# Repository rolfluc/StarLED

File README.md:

Simply a 4x Series 2x Parallel LED board to use the star shaped board designs that are seen by OSRAM

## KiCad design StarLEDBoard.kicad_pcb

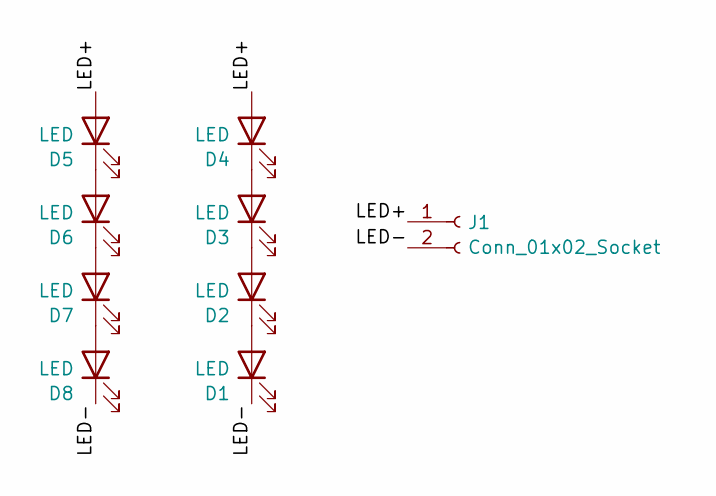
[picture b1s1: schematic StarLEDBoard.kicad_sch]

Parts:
D1, D2, D3, D4, D5, D6, D7, D8: LED; LED_Everlight-SMD3528_3.5x2.8mm_67-21ST
J1: Conn_01x02_Socket; LEDConnector

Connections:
/LED+: D4.2 (A), D5.2 (A), J1.1
/LED-: D1.1 (K), D8.1 (K), J1.2
unnamed: D1.2 (A), D2.1 (K)
unnamed: D2.2 (A), D3.1 (K)
unnamed: D3.2 (A), D4.1 (K)
unnamed: D5.1 (K), D6.2 (A)
unnamed: D6.1 (K), D7.2 (A)
unnamed: D7.1 (K), D8.2 (A)

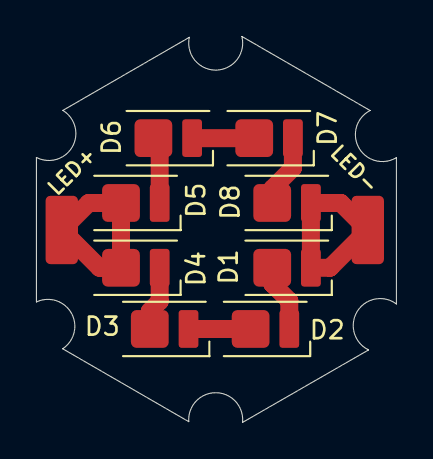
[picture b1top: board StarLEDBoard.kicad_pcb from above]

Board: 2 copper layers, 20.0 x 21.4 mm, 9 parts (0 on the bottom side), 8 nets.

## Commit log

2025-10-28 First Comit, Basic Schematic
2025-10-28 Board Outline Locked
2025-10-28 Ordered Board
